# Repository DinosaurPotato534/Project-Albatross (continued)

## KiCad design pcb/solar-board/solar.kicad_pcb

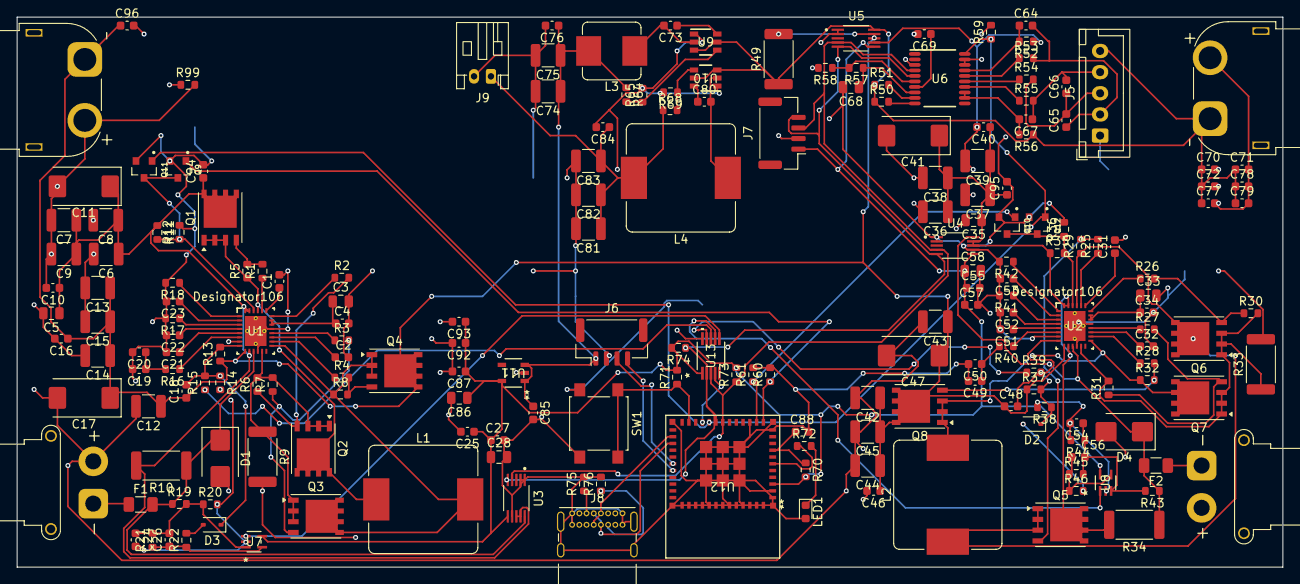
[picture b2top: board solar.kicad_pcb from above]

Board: 2 copper layers, 149.6 x 65.0 mm, 201 parts (0 on the bottom side), 104 nets.

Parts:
C1, C2, C4, C10, C16, C21, C23, C24, C25, C27, C31, C32, C34, C40, C46, C51, C53, C54, C55, C57, C64, C65, C66, C67, C69, C72, C73, C76, C79, C80, C84, C87, C92, C94, C95, C96: 100n; C_0603_1608Metric
C3, C33, C86: 10u; C_0805_2012Metric
C5, C28, C35, C58, C68: 1u; C_0805_2012Metric
C6, C7, C8, C9, C12, C13, C14, C15, C36, C37, C38, C39, C42, C43, C44, C45, C74, C75, C81, C82, C83: 22u; C_1210_3225Metric
C11, C17, C41, C47: 100u_poly; CP_EIA-7343-31_Kemet-D
C18, C48: 22p; C_0603_1608Metric
C19, C49: 4.7n; C_0603_1608Metric
C20, C50: 100p; C_0603_1608Metric
C22, C52: 390p; C_0603_1608Metric
C26, C56: 22n; C_0603_1608Metric
C70, C71, C77, C78: 10u; C_0603_1608Metric
C85, C88, C93: 1u; C_0603_1608Metric
D1, D4: SMBJ45A; D_SMB
D2, D3: BAT54; D_SOD-323
F1, F2: 10A; Fuse_1206_3216Metric
J1: XT30_panelA; AMASS_XT30PW-F_1x02_P2.50mm_Horizontal
J2: XT30_panelB; AMASS_XT30PW-F_1x02_P2.50mm_Horizontal
J3: XT60_battery; AMASS_XT60PW-F_1x02_P7.20mm_Horizontal
J4: XT60_ESCout; AMASS_XT60PW-F_1x02_P7.20mm_Horizontal
J5: JST-XH_balance; JST_XH_B5B-XH-A_1x05_P2.50mm_Vertical
J6: JST-GH_toFC; JST_GH_BM04B-GHS-TBT_1x04-1MP_P1.25mm_Vertical
J7: JST-GH_I2C; JST_GH_BM04B-GHS-TBT_1x04-1MP_P1.25mm_Vertical
J8: USB_C_Receptacle_USB2.0_16P; USB_C_Receptacle_GCT_USB4085
J9: JST-PH_servo; JST_PH_S2B-PH-K_1x02_P2.00mm_Horizontal
L1, L2: 10uH SRP1245A-100M; L_Bourns_SRP1245A
L3: 10uH SRP7028A-100M; L_Bourns_SRP7028A_7.3x6.6mm
L4: 6.8uH SRP1245A-6R8M; L_Bourns_SRP1245A
LED1: green; LED_0603_1608Metric
Q1, Q2, Q3, Q4, Q5, Q6, Q7, Q8: SIR626DP; PowerPAK_SO-8_Single
Q9, Q10, Q11, Q12: Q_NMOS_GSD; TRANS_2N7002
R1, R2, R3, R4, R25, R26, R27, R28: 2.2; R_0603_1608Metric
R5, R6, R7, R8, R12, R14, R16, R20, R29, R30, R31, R32, R36, R38, R40, R44, R57, R60, R61, R65, R69, R70, R71: 10k; R_0603_1608Metric
R9, R33: 10m; R_2512_6332Metric
R10, R34: 5m; R_2512_6332Metric
R11, R35: 22.1k; R_0603_1608Metric
R13, R37: 130k; R_0603_1608Metric
R15, R39: 33k; R_0603_1608Metric
R17, R41: 84.5k; R_0603_1608Metric
R18, R42: 93.1k; R_0603_1608Metric
R19, R43: 120k; R_0603_1608Metric
R21, R45: 1M; R_0603_1608Metric
R22, R46: 4.7k; R_0603_1608Metric
R49: 1m; R_2512_6332Metric
R50, R51, R52, R53, R54, R55, R56: 100; R_0603_1608Metric
R58: 10k_NTC; R_0603_1608Metric
R59: 100k; R_0603_1608Metric
R64: 75k; R_0603_1608Metric
R68: 90.9k; R_0603_1608Metric
R72: 1k; R_0603_1608Metric
R73, R74: 2.2k; R_0603_1608Metric
R75, R76: 5.1k; R_0603_1608Metric
R99: 0R; R_0603_1608Metric
SW1: tact; SW_SPST_B3S-1000
U1, U2: LM5175RHFR; RHF0028A
U3, U4, U5: INA228AIDGSR; SOP50P490X110-10N
U6: BQ7692000PWR; PW0020A_N
U7, U8: TLV9061IDCKR; DCK5_TEX
U9: TPS54202DDCR; DDC0006A_N
U10: TPS54302DDCR; DDC0006A_N
U11: AP2112K-3.3TRG1; SOT_RG1_DIO
U12: ESP32-C3-MINI-1-N4; ESP32-C3-MINI-1_EXP
U13: MCP4728A0T-E_UN; MSOP10_MC_MCH

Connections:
/+3V3: C25.1, C27.1, C28.1, C55.1, C57.1, C58.1, C86.1, C87.1, C92.1, C93.1, J7.1, R70.2, R71.2, R73.2, R74.2, U3.6 (VS), U4.6 (VS), U5.6 (VS), U7.5 (V+), U8.5 (V+), U11.5 (VOUT), U12.3 (3V3), U13.1 (VDD)
/+5V: C74.1, C75.1, C76.1, C85.1, J6.1, L3.2, R64.1, U11.1 (VIN), U11.3 (EN)
/+6V: C81.1, C82.1, C83.1, C84.1, J9.1, L4.2, R68.1
/AGND: C19.2, C20.2, C21.2, C22.2, C23.2, C24.2, C25.2, C27.2, C28.2, C49.2, C50.2, C51.2, C52.2, C53.2, C54.2, C55.2, C57.2, C58.2, C68.2, C69.2, C85.2, C86.2, C87.2, C88.2, C92.2, C93.2, C94.2, C95.2, C96.2, J7.2, J8.A1 (GND), J8.A12 (GND), J8.B1 (GND), J8.B12 (GND), J8.SH (SHIELD), LED1.2 (A), Q9.2, Q10.2, Q11.2, Q12.2, R12.2, R14.2, R17.2, R18.2, R20.2, R36.2, R38.2, R41.2, R42.2, R44.2, R58.2, R59.2, R60.2, R61.2, R75.2, R76.2, R99.1, SW1.2, U1.7 (AGND), U2.7 (AGND), U3.1 (A1), U3.2 (A0), U3.7 (GND), U4.1 (A1), U4.2 (A0), U4.7 (GND), U5.1 (A1), U5.2 (A0), U6.3 (VSS), U6.18 (SRP), U6.19 (SRN), U7.2 (V-), U8.2 (V-), U11.2 (GND), U12.1 (GND), U12.2 (GND), U12.11 (GND), U12.14 (GND), U12.36 (GND), U12.37 (GND), U12.38 (GND), U12.39 (GND), U12.40 (GND), U12.41 (GND), U12.42 (GND), U12.43 (GND), U12.44 (GND), U12.45 (GND), U12.46 (GND), U12.47 (GND), U12.48 (GND), U12.49 (GND), U12.50 (GND), U12.51 (GND), U12.52 (GND), U12.53 (GND), U12.54 (GND), U12.55 (GND), U12.56 (GND), U12.57 (GND), U12.58 (GND), U12.59 (GND), U12.60 (GND), U12.61 (GND), U13.10 (VSS)
/BMS_ALERT: Q11.1, Q12.1, R59.1, U6.20 (ALERT), U12.20 (IO6)
/BOOT1_A: C1.1, U1.23 (BOOT1)
/BOOT1_B: C31.1, U2.23 (BOOT1)
/BOOT2_A: C2.1, U1.17 (BOOT2)
/BOOT2_B: C32.1, U2.17 (BOOT2)
/BOOT_5V: C73.1, U9.6 (BOOT)
/BOOT_6V: C80.1, U10.6 (BOOT)
/BOOT_BTN: R71.1, SW1.1, U12.23 (IO9)
/BQ_BAT: R50.2, U6.10 (BAT)
/BQ_CAP1: C69.1, U6.7 (CAP1)
/BQ_REGOUT: C68.1, R57.1, U6.8 (REGOUT)
/BQ_REGSRC: R51.2, U6.9 (REGSRC)
/BQ_TS1: R57.2, R58.1, U6.6 (TS1)
/CELL1: C64.2, C65.1, J5.2, R53.2
/CELL2: C65.2, C66.1, J5.3, R54.2
/CELL3: C66.2, C67.1, J5.4, R55.2
/CMPM_A: C19.1, C20.1, R16.2
/CMPM_B: C49.1, C50.1, R40.2
/COMP_A: R16.1, U1.6 (COMP)
/COMP_B: R40.1, U2.6 (COMP)
/CSP_A: Q2.1 (S), Q2.2 (S), Q2.3 (S), Q3.1 (S), Q3.2 (S), Q3.3 (S), R6.2, R7.2, R9.1, U1.13 (CS)
/CSP_B: Q6.1 (S), Q6.2 (S), Q6.3 (S), Q7.1 (S), Q7.2 (S), Q7.3 (S), R30.2, R31.2, R33.1, U2.13 (CS)
/DAC_CV_A: R15.1, U13.8 (VOUTC)
/DAC_CV_B: R39.1, U13.9 (VOUTD)
/DAC_LDAC: U12.21 (IO7), U13.4 (*LDAC)
/DAC_MPPT_A: U7.1 (IN+), U13.6 (VOUTA)
/DAC_MPPT_B: U8.1 (IN+), U13.7 (VOUTB)
/DITH_A: C23.1, U1.2 (DITH)
/DITH_B: C53.1, U2.2 (DITH)
/EN_A: Q9.3, Q11.3, R11.2, R12.1, U1.26 (EN_UVLO)
/EN_A_CTL: Q9.1, R60.1, U12.12 (IO0)
/EN_B: Q10.3, Q12.3, R35.2, R36.1, U2.26 (EN_UVLO)
/EN_B_CTL: Q10.1, R61.1, U12.13 (IO1)
/FB_5V: R64.2, R65.1, U9.4 (FB)
/FB_6V: R68.2, R69.1, U10.4 (FB)
/FB_A: C18.2, D3.1 (K), R13.2, R14.1, R15.2, U1.8 (FB)
/FB_B: C48.2, D2.1 (K), R37.2, R38.1, R39.2, U2.8 (FB)
/FC_RX: J6.3, U12.30 (RXD0)
/FC_TX: J6.4, U12.31 (TXD0)
/G1_A: Q1.4 (G), R1.2, R5.2
/G1_B: Q5.4 (G), R25.2, R29.2
/G2_A: Q2.4 (G), R2.2, R6.1
/G2_B: Q6.4 (G), R26.2, R30.1
/G3_A: Q3.4 (G), R3.2, R7.1
/G3_B: Q7.4 (G), R27.2, R31.1
/G4_A: Q4.4 (G), R4.2, R8.2
/G4_B: Q8.4 (G), R28.2, R32.2
/HDRV1_A: R1.1, U1.24 (HDRV1)
/HDRV1_B: R25.1, U2.24 (HDRV1)
/HDRV2_A: R4.1, U1.16 (HDRV2)
/HDRV2_B: R28.1, U2.16 (HDRV2)
/INJ_A: D3.2 (A), R22.2
/INJ_B: D2.2 (A), R46.2
/LDRV1_A: R2.1, U1.22 (LDRV1)
/LDRV1_B: R26.1, U2.22 (LDRV1)
/LDRV2_A: R3.1, U1.18 (LDRV2)
/LDRV2_B: R27.1, U2.18 (LDRV2)
/LED_A: LED1.1 (K), R72.2
/LED_DRV: R72.1, U12.6 (IO3)
/MCU_EN: C88.1, R70.1, U12.8 (EN)
/MODE_A: R18.1, U1.1 (MODE)
/MODE_B: R42.1, U2.1 (MODE)
/OPA_A: C26.1, R21.1, R22.1, U7.4 (OUT)
/OPA_B: C56.1, R45.1, R46.1, U8.4 (OUT)
/PACK_P: C70.1, C71.1, C72.1, C77.1, C78.1, C79.1, J3.1, J5.5, R49.1, R50.1, R51.1, R56.1, U5.10 (IN+), U9.3 (VIN), U9.5 (EN), U10.3 (VIN), U10.5 (EN)
/PGND: C1.2, C2.2, C3.2, C4.2, C5.2, C6.2, C7.2, C8.2, C9.2, C10.2, C11.2, C12.2, C13.2, C14.2, C15.2, C16.2, C17.2, C31.2, C32.2, C33.2, C34.2, C35.2, C36.2, C37.2, C38.2, C39.2, C40.2, C41.2, C42.2, C43.2, C44.2, C45.2, C46.2, C47.2, C70.2, C71.2, C72.2, C74.2, C75.2, C76.2, C77.2, C78.2, C79.2, C81.2, C82.2, C83.2, C84.2, D1.2 (A2), D4.2 (A2), J1.2, J2.2, J3.2, J4.2, J5.1, J6.2, J9.2, R9.2, R33.2, R52.1, R65.2, R69.2, R99.2, U1.12 (CSG), U1.19 (PGND), U1.29 (PAD), U2.12 (CSG), U2.19 (PGND), U2.29 (PAD), U5.7 (GND), U9.1 (GND), U10.1 (GND)
/RT_A: R17.1, U1.3 (RT)
/RT_B: R41.1, U2.3 (RT)
/SCL: J7.4, R74.1, U3.5 (SCL), U4.5 (SCL), U5.5 (SCL), U6.5 (SCL), U12.19 (IO5), U13.2 (SCL)
/SDA: J7.3, R73.1, U3.4 (SDA), U4.4 (SDA), U5.4 (SDA), U6.4 (SDA), U12.18 (IO4), U13.3 (SDA)
/SLOPE_A: C22.1, U1.4 (SLOPE)
/SLOPE_B: C52.1, U2.4 (SLOPE)
/SOL_A_IN: F1.1, J1.1
/SOL_A_P: D1.1 (A1), F1.2, R10.1, R19.1, U1.11 (ISNS+), U3.10 (IN+)
/SOL_B_IN: F2.1, J2.1
/SOL_B_P: D4.1 (A1), F2.2, R34.1, R43.1, U2.11 (ISNS+), U4.10 (IN+)
/SS_A: C21.1, U1.5 (SS)
/SS_B: C51.1, U2.5 (SS)
/SW1_A: L1.1, Q1.1 (S), Q1.2 (S), Q1.3 (S), Q2.5 (D), R5.1, U1.25 (SW1)
/SW1_B: L2.1, Q5.1 (S), Q5.2 (S), Q5.3 (S), Q6.5 (D), R29.1, U2.25 (SW1)
/SW2_A: L1.2, Q3.5 (D), Q4.1 (S), Q4.2 (S), Q4.3 (S), R8.1, U1.15 (SW2)
/SW2_B: L2.2, Q7.5 (D), Q8.1 (S), Q8.2 (S), Q8.3 (S), R32.1, U2.15 (SW2)
/SW_5V: C73.2, L3.1, U9.2 (SW)
/SW_6V: C80.2, L4.1, U10.2 (SW)
/USB_CC1: J8.A5 (CC1), R75.1
/USB_CC2: J8.B5 (CC2), R76.1
/USB_DM: J8.A7 (D-), J8.B7 (D-), U12.26 (IO18)
/USB_DP: J8.A6 (D+), J8.B6 (D+), U12.27 (IO19)
/VC0: C64.1, R52.2, U6.17 (VC0)
/VC1: R53.1, U6.16 (VC1)
/VC2: R54.1, U6.15 (VC2)
/VC3: R55.1, U6.14 (VC3)
/VC4: C67.2, R56.2, U6.12 (VC5), U6.13 (VC4)
/VCC_A: C3.1, C4.1, U1.20 (VCC), U1.21 (BIAS)
/VCC_B: C33.1, C34.1, U2.20 (VCC), U2.21 (BIAS)
/VIN_A: C5.1, C6.1, C7.1, C8.1, C9.1, C10.1, C11.1, C94.1, Q1.5 (D), R10.2, R11.1, U1.10 (ISNS-), U1.27 (VIN), U1.28 (VINSNS), U3.8 (VBUS), U3.9 (IN-)
/VIN_B: C35.1, C36.1, C37.1, C38.1, C39.1, C40.1, C41.1, C95.1, Q5.5 (D), R34.2, R35.1, U2.10 (ISNS-), U2.27 (VIN), U2.28 (VINSNS), U4.8 (VBUS), U4.9 (IN-)
/VPACK: C12.1, C13.1, C14.1, C15.1, C16.1, C17.1, C18.1, C42.1, C43.1, C44.1, C45.1, C46.1, C47.1, C48.1, C96.1, J4.1, Q4.5 (D), Q8.5 (D), R13.1, R37.1, R49.2, U1.9 (VOSNS), U2.9 (VOSNS), U5.8 (VBUS), U5.9 (IN-)
/VPAN_A: C24.1, C26.2, R19.2, R20.1, R21.2, U7.3 (IN-)
/VPAN_B: C54.1, C56.2, R43.2, R44.1, R45.2, U8.3 (IN-)
